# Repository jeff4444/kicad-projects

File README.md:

# KiCad Projects

A collection of custom PCB designs created in KiCad for various electronics projects.

## Projects

### � [Project Lux - Free-Space Optical Audio Link](./FSO/)
A laser-based audio communication system developed for the Howard University **IEEE H.O.P.E. (Hands-On PCB Engineering)** Project (Fall 2025). This sophisticated project demonstrates optical communication principles by transmitting high-fidelity audio over a laser beam.

#### [Transmitter Board](./FSO/Transmitter%20board/)
Modulates a 3.5mm audio input signal onto a laser diode using a transconductance stage with op-amps and transistors.

#### [Receiver Board](./FSO/Receiver%20board/)
Uses **BPW34** photodiodes with a transimpedance amplifier (TIA), voltage pre-amplification via **LM358**, and a **PAM8403D** Class-D audio amplifier to drive speakers.

---

### �🔊 [Audio Amplifier](./audio_amplifier/)
A low voltage audio power amplifier board based on the **LM386** IC. Perfect for small speaker applications requiring simple audio amplification from line-level sources.

### 📡 [Proximity Sensor](./proximity_sensor/)
An LED bar graph display board using the **LM3914** dot/bar display driver. Provides a visual representation of an analog signal level through a 10-LED bar graph display.

### 🤖 Recyclobot System
The Recyclobot is a robotics project consisting of two main PCBs:

#### [Controller](./recyclobot/controller/)
An RF remote control encoder board using the **HT12E** serial encoder IC. This board encodes button presses and transmits commands wirelessly to the motherboard.

#### [Motherboard](./recyclobot/motherboard/)
The main control board for the Recyclobot, featuring an **L293D** quadruple half-H motor driver. Receives wireless commands and controls DC motors for robot movement.

---

## Directory Structure

```
kicad-projects/
├── FSO/                 # Project Lux - Free-space optical audio link
│   ├── Receiver board/  # Photodiode array + TIA + audio amp
│   └── Transmitter board/ # Laser modulation circuit
├── audio_amplifier/     # LM386 audio amplifier board
├── proximity_sensor/    # LM3914 LED bar graph display
└── recyclobot/
    ├── controller/      # HT12E RF remote encoder
    └── motherboard/     # L293D motor driver board
```

## Getting Started

Each project directory contains:
- `.kicad_sch` - Schematic file
- `.kicad_pcb` - PCB layout file
- `.kicad_pro` - Project file
- `board.png` - Visual preview of the PCB design
- `gerbers/` - Manufacturing files (where available)

Open the `.kicad_pro` file in KiCad 8.0 or later to view and edit the designs.

## License

Personal electronics projects.

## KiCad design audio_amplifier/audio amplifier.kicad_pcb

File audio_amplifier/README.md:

# Audio Amplifier

A compact low voltage audio power amplifier PCB based on the **LM386** integrated circuit.

## Overview

This board provides simple audio amplification suitable for driving small speakers from line-level audio sources. The LM386 is a popular choice for battery-powered audio applications due to its low power consumption and minimal external component requirements.

## Key Features

- **LM386 Audio Power Amplifier IC**
  - Wide operating voltage range: 4V to 12V
  - Built-in gain control (20-200)
  - Low quiescent current for battery operation
  
- **Connectors for:**
  - Audio input
  - Speaker output
  - Power supply

## Specifications

| Parameter | Value |
|-----------|-------|
| Main IC | LM386 |
| Operating Voltage | 4V - 12V |
| Power Output | ~1W (into 8Ω @ 12V) |
| Package | DIP-8 |

## Applications

- Portable audio devices
- DIY speaker projects
- Guitar practice amplifiers
- Intercom systems
- Audio signal boosters

## Files

- `audio amplifier.kicad_sch` - Schematic
- `audio amplifier.kicad_pcb` - PCB layout
- `audio amplifier.kicad_pro` - KiCad project file
- `gerber_gen/` - Manufacturing files

## References

- [LM386 Datasheet (TI)](http://www.ti.com/lit/ds/symlink/lm386.pdf)

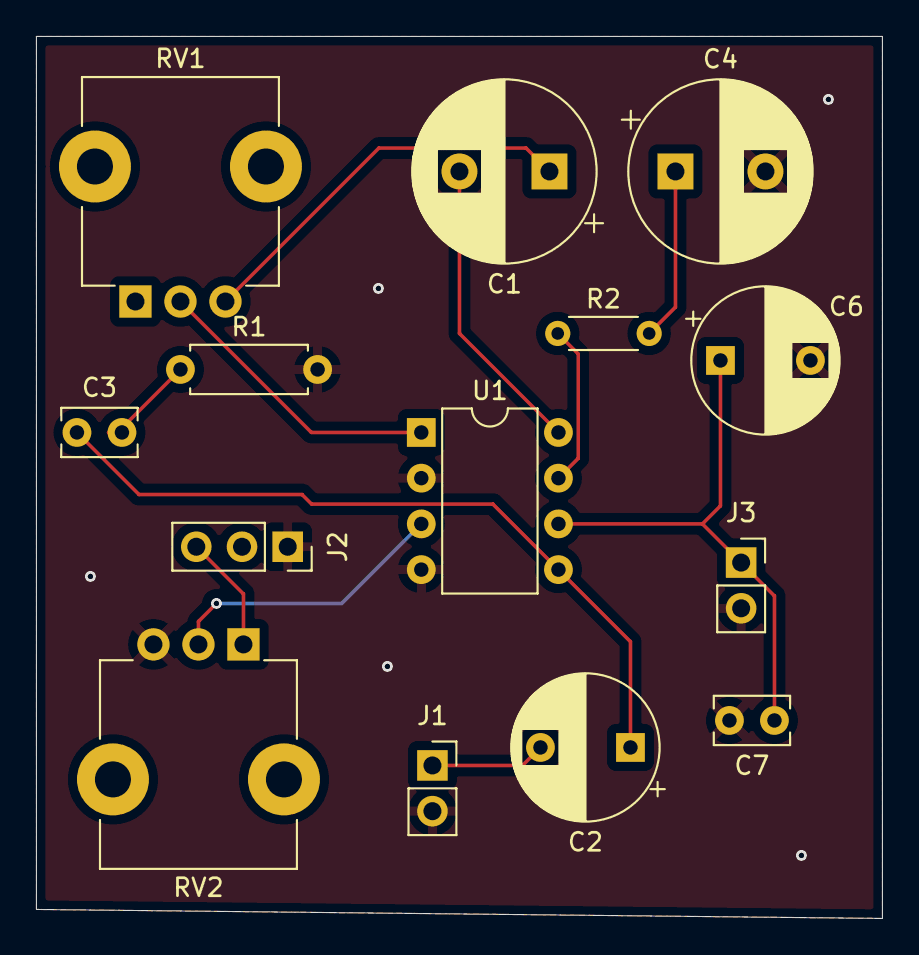
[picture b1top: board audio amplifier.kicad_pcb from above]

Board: 2 copper layers, 47.0 x 49.0 mm, 14 parts (0 on the bottom side), 12 nets.

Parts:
C1, C4: C_Polarized_US; CP_Radial_D10.0mm_P5.00mm
C2, C6: C_Polarized_US; CP_Radial_D8.0mm_P5.00mm
C3, C7: C; C_Rect_L4.0mm_W2.5mm_P2.50mm
J1, J3: Conn_01x02_Socket; PinSocket_1x02_P2.54mm_Vertical
J2: Conn_01x03_Socket; PinSocket_1x03_P2.54mm_Vertical
R1: R_US; R_Axial_DIN0207_L6.3mm_D2.5mm_P7.62mm_Horizontal
R2: R_US; R_Axial_DIN0204_L3.6mm_D1.6mm_P5.08mm_Horizontal
RV1, RV2: R_Potentiometer_US; Potentiometer_TT_P0915N
U1: LM386; DIP-8_W7.62mm

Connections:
+9V: C6.1, C7.1, J3.1, U1.6 (V+)
GND: C4.2, C6.2, C7.2, J1.2, J2.1, J3.2, R1.2, RV2.3, U1.2 (-), U1.4 (GND)
unnamed: C1.1, RV1.3
unnamed: C1.2, U1.8 (GAIN)
unnamed: C2.1, C3.1, U1.5
unnamed: C3.2, R1.1
unnamed: C4.1, R2.2
unnamed: C2.2, J1.1
unnamed: J2.3, RV2.1
unnamed: RV1.2, U1.1 (GAIN)
unnamed: RV2.2, U1.3 (+)
unnamed: R2.1, U1.7 (BYPASS)

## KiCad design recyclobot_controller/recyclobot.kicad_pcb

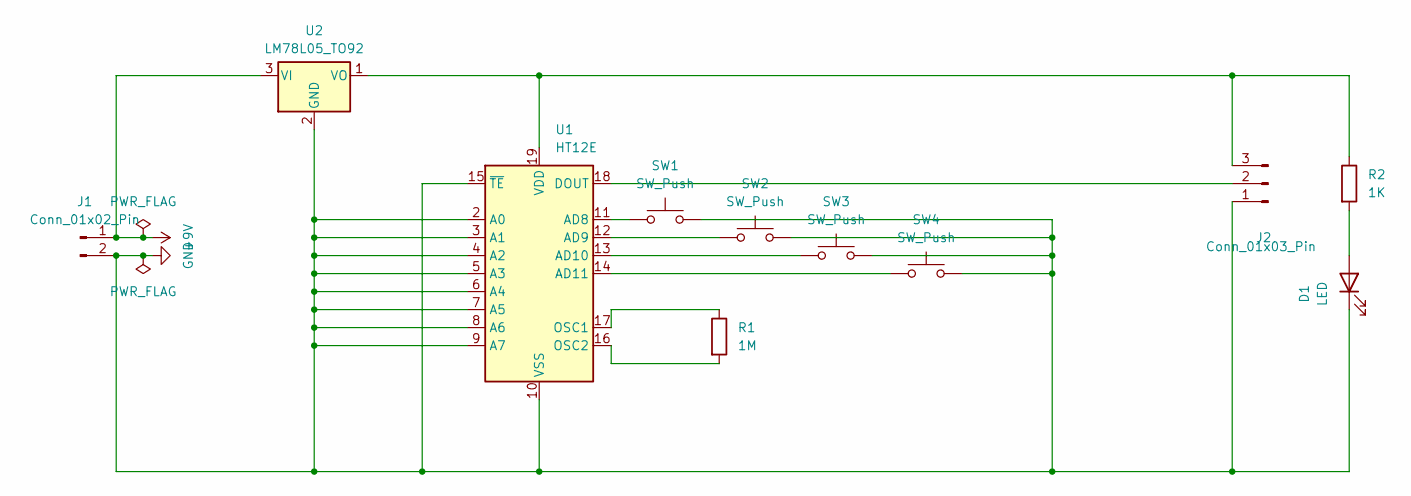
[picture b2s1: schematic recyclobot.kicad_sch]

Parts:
D1: LED; LED_D5.0mm
J1: Conn_01x02_Pin; PinSocket_1x02_P2.54mm_Vertical
J2: Conn_01x03_Pin; PinSocket_1x03_P2.54mm_Vertical
R1: 1M; R_Axial_DIN0207_L6.3mm_D2.5mm_P10.16mm_Horizontal
R2: 1K; R_Axial_DIN0207_L6.3mm_D2.5mm_P10.16mm_Horizontal
SW1, SW2, SW3, SW4: SW_Push; SW_Tactile_Straight_KSA0Axx1LFTR
U1: HT12E; SOP-20_7.5x12.8mm_P1.27mm
U2: LM78L05_TO92; TO-92_Inline_W4.0mm_Horizontal_FlatSideUp

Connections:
+9V: J1.1, U2.3 (VI)
GND: D1.1 (K), J1.2, J2.1, SW1.2, SW2.2, SW3.2, SW4.2, U1.2 (A0), U1.3 (A1), U1.4 (A2), U1.5 (A3), U1.6 (A4), U1.7 (A5), U1.8 (A6), U1.9 (A7), U1.10 (VSS), U1.15 (~TE), U2.2 (GND)
unnamed: D1.2 (A), R2.2
unnamed: J2.2, U1.18 (DOUT)
unnamed: J2.3, R2.1, U1.19 (VDD), U2.1 (VO)
unnamed: SW1.1, U1.11 (AD8)
unnamed: SW2.1, U1.12 (AD9)
unnamed: SW3.1, U1.13 (AD10)
unnamed: SW4.1, U1.14 (AD11)
unnamed: R1.1, U1.17 (OSC1)
unnamed: R1.2, U1.16 (OSC2)

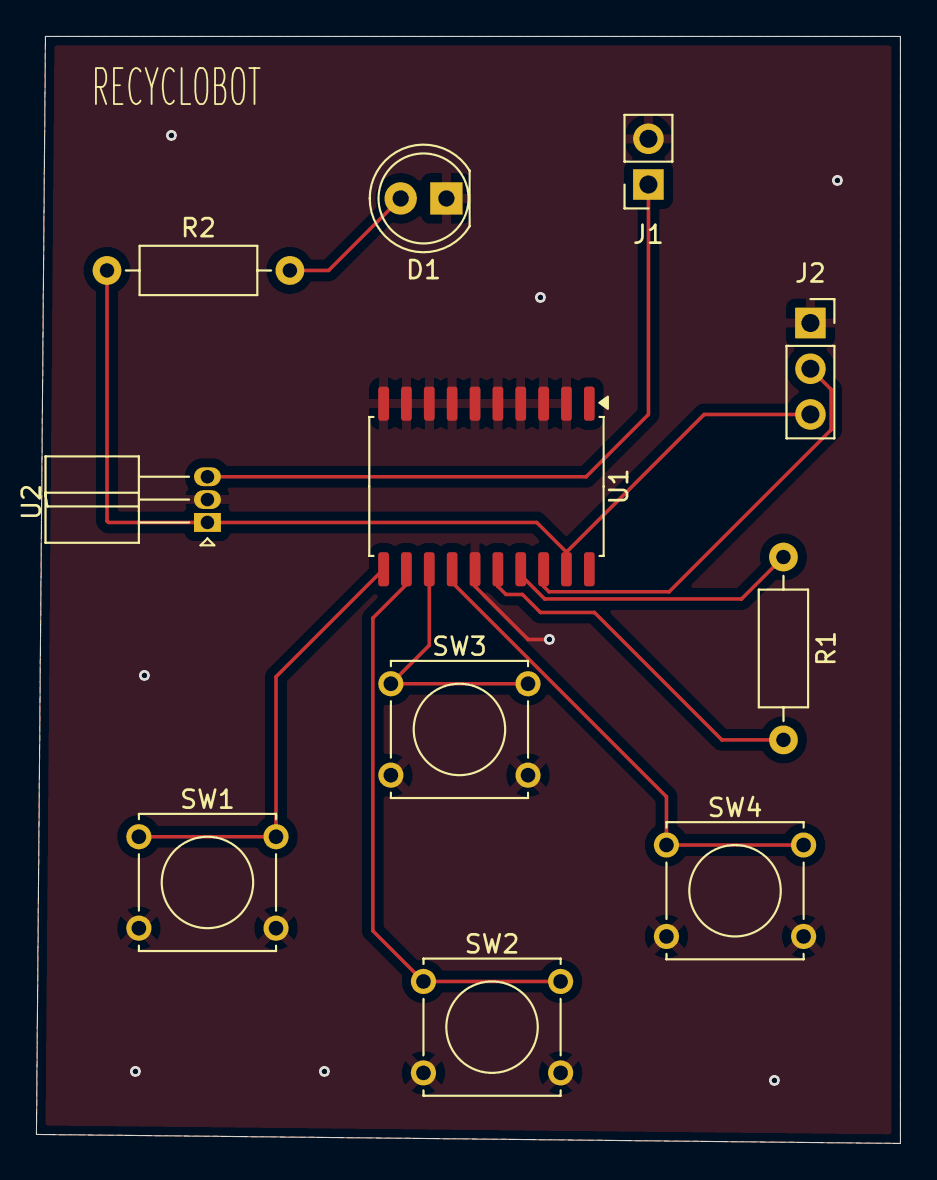
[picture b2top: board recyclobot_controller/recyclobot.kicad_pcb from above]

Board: 2 copper layers, 48.0 x 61.5 mm, 11 parts (0 on the bottom side), 11 nets.

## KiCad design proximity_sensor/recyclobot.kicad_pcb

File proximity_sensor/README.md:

# Proximity Sensor Display

An LED bar graph display PCB using the **LM3914** dot/bar display driver IC.

## Overview

This board provides a visual 10-LED bar graph display to represent an analog signal level. The LM3914 scales the input voltage linearly across its outputs, illuminating LEDs progressively as the signal increases. This is commonly used with proximity/distance sensors to provide a visual indication of signal strength or distance.

## Key Features

- **LM3914 Dot/Bar Display Driver IC**
  - 10 individually controlled LED outputs
  - Linear scale display
  - Selectable dot or bar display mode
  - Internal voltage reference
  
- **10 LEDs** for visual signal representation

- **Connectors for:**
  - Analog signal input
  - Power supply

## Specifications

| Parameter | Value |
|-----------|-------|
| Main IC | LM3914 |
| Display Mode | Dot or Bar (configurable) |
| LED Outputs | 10 |
| Package | DIP-18 |
| Operating Voltage | 3V - 25V |

## Applications

- Proximity/distance sensor displays
- Audio level meters (VU meters)
- Battery level indicators
- Signal strength meters
- Temperature displays

## How It Works

The LM3914 contains a precision 10-step voltage divider that compares the input signal against internal reference points. As the input voltage rises, more LEDs illuminate to provide a visual representation of the signal magnitude.

## Files

- `recyclobot.kicad_sch` - Schematic
- `recyclobot.kicad_pcb` - PCB layout
- `gerbers/` - Manufacturing files

## References

- [LM3914 Datasheet (TI)](https://www.ti.com/lit/ds/symlink/lm3914.pdf)

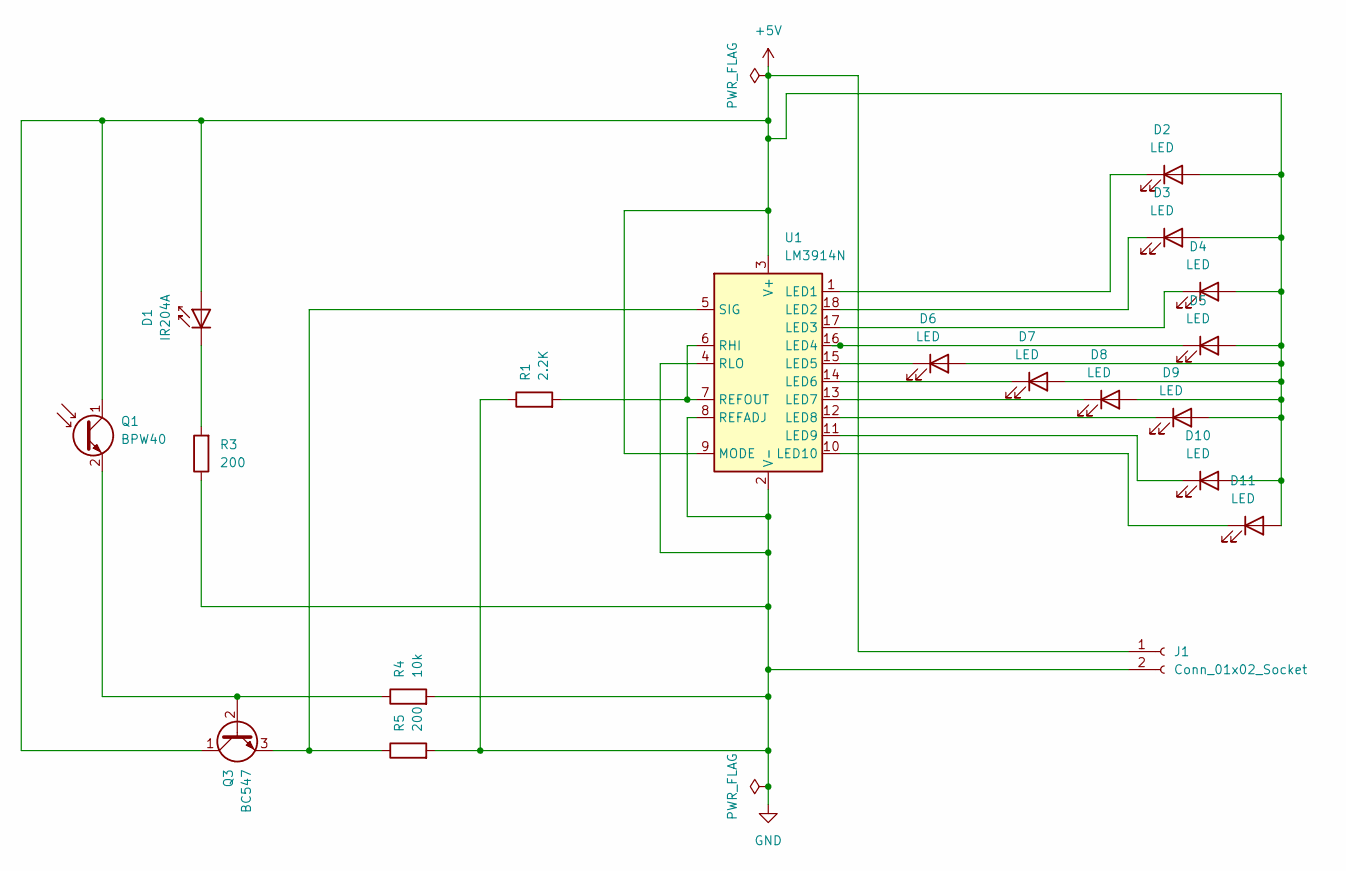
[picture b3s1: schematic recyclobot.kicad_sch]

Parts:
D1: IR204A; LED_D3.0mm_IRBlack
D2, D3, D4, D5, D6, D7, D8, D9, D10, D11: LED; LED_D3.0mm
J1: Conn_01x02_Socket; PinSocket_1x02_P2.54mm_Vertical
Q1: BPW40; LED_D5.0mm_Clear
Q3: BC547; TO-92_Inline
R1: 2.2K; R_Axial_DIN0204_L3.6mm_D1.6mm_P7.62mm_Horizontal
R3, R5: 200; R_Axial_DIN0204_L3.6mm_D1.6mm_P7.62mm_Horizontal
R4: 10k; R_Axial_DIN0204_L3.6mm_D1.6mm_P7.62mm_Horizontal
U1: LM3914N; DIP-18_W7.62mm

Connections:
+5V: D1.2 (A), D2.2 (A), D3.2 (A), D4.2 (A), D5.2 (A), D6.2 (A), D7.2 (A), D8.2 (A), D9.2 (A), D10.2 (A), D11.2 (A), J1.1, Q1.1 (C), Q3.1 (C), U1.3 (V+), U1.9 (MODE)
GND: J1.2, R1.1, R3.1, R4.2, R5.2, U1.2 (V-), U1.4 (RLO), U1.8 (REFADJ)
unnamed: D1.1 (K), R3.2
unnamed: D2.1 (K), U1.1 (LED1)
unnamed: D3.1 (K), U1.18 (LED2)
unnamed: D4.1 (K), U1.17 (LED3)
unnamed: D5.1 (K), U1.16 (LED4)
unnamed: D6.1 (K), U1.15 (LED5)
unnamed: D7.1 (K), U1.14 (LED6)
unnamed: D8.1 (K), U1.13 (LED7)
unnamed: D9.1 (K), U1.12 (LED8)
unnamed: D10.1 (K), U1.11 (LED9)
unnamed: D11.1 (K), U1.10 (LED10)
unnamed: Q1.2 (E), Q3.2 (B), R4.1
unnamed: Q3.3 (E), R5.1, U1.5 (SIG)
unnamed: R1.2, U1.6 (RHI), U1.7 (REFOUT)

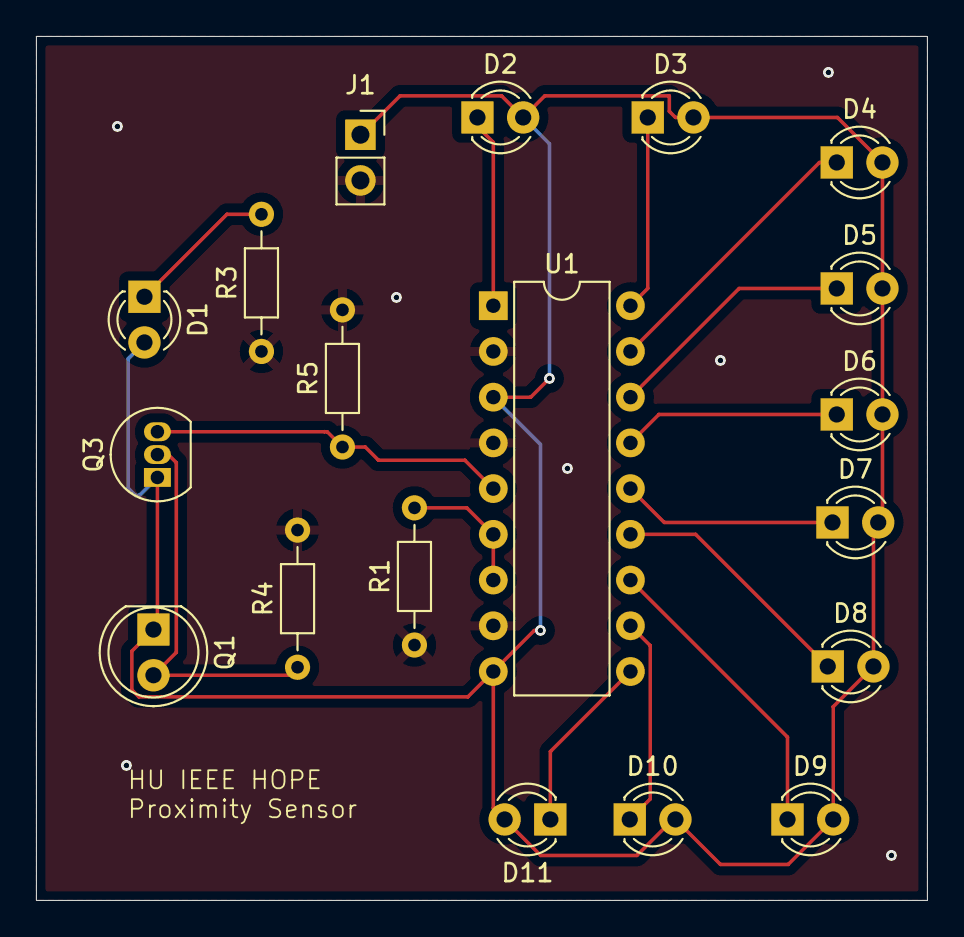
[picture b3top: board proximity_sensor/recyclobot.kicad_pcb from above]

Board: 2 copper layers, 49.5 x 48.0 mm, 19 parts (0 on the bottom side), 16 nets.

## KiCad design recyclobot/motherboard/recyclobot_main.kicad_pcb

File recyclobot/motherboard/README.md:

# Recyclobot Motherboard

The main motor driver PCB for the Recyclobot, featuring the **L293D** quadruple half-H motor driver IC.

## Overview

This board is the central control unit for the Recyclobot project. It receives wireless commands from the remote controller and drives DC motors to move the robot. The L293D provides bidirectional control for two DC motors with built-in protection diodes.

## Key Features

- **L293D Quadruple Half-H Motor Driver IC**
  - Dual full-bridge configuration for 2 motors
  - Bidirectional motor control (forward/reverse)
  - Built-in flyback diodes
  - Separate logic and motor supply voltages
  
- **LED indicators** for power and status

- **Connectors for:**
  - DC motor outputs (2 motors)
  - RF receiver module
  - Power supply
  - Sensor inputs

## Specifications

| Parameter | Value |
|-----------|-------|
| Main IC | L293D |
| Motor Channels | 2 (bi-directional) |
| Logic Voltage | 5V |
| Motor Voltage | 4.5V - 36V |
| Output Current | 600mA per channel (1.2A peak) |
| Package | DIP-16 |

## System Integration

This motherboard receives commands from the **Recyclobot Controller** via wireless RF link.

```
┌─────────────────┐                   ┌─────────────────┐
│   Controller    │     RF Signal     │   Motherboard   │
│     (HT12E)     │ ─────────────────▶│     (L293D)     │
└─────────────────┘                   └────────┬────────┘
                                               │
                                    ┌──────────┴──────────┐
                                    │                     │
                              ┌─────▼─────┐         ┌─────▼─────┐
                              │  Motor 1  │         │  Motor 2  │
                              │  (Left)   │         │  (Right)  │
                              └───────────┘         └───────────┘
```

## Motor Control Truth Table

| EN | IN1 | IN2 | Motor Action |
|----|-----|-----|--------------|
| H  | L   | H   | Forward      |
| H  | H   | L   | Reverse      |
| H  | L   | L   | Coast/Stop   |
| H  | H   | H   | Brake        |
| L  | X   | X   | Disabled     |

## Files

- `recyclobot_main.kicad_sch` - Schematic
- `recyclobot_main.kicad_pcb` - PCB layout
- `gerbers/` - Manufacturing files

## References

- [L293D Datasheet (TI)](http://www.ti.com/lit/ds/symlink/l293.pdf)

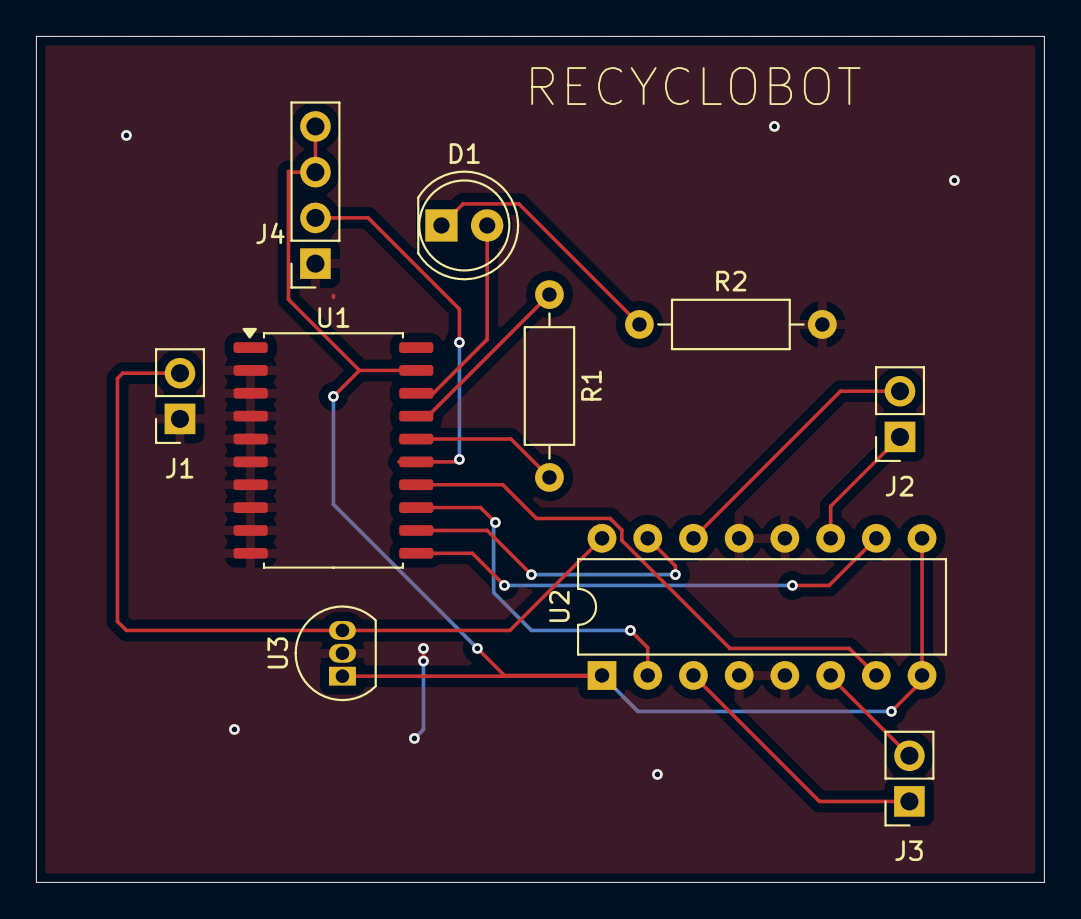
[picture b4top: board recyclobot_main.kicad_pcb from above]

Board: 2 copper layers, 56.0 x 47.0 mm, 10 parts (0 on the bottom side), 16 nets.

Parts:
D1: LED; LED_D5.0mm
J1, J2, J3: Conn_01x02_Socket; PinSocket_1x02_P2.54mm_Vertical
J4: Conn_01x04_Socket; PinSocket_1x04_P2.54mm_Vertical
R1: 33K; R_Axial_DIN0207_L6.3mm_D2.5mm_P10.16mm_Horizontal
R2: 1K; R_Axial_DIN0207_L6.3mm_D2.5mm_P10.16mm_Horizontal
U1: HT12D; SOP-20_7.5x12.8mm_P1.27mm
U2: L293D; DIP-16_W7.62mm
U3: LM78L05_TO92; TO-92_Inline

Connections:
+9V: J1.2, U2.16 (VCC1), U3.3 (VI)
GND: J1.1, J4.1, R2.2, U1.2 (A0), U1.3 (A1), U1.4 (A2), U1.5 (A3), U1.6 (A4), U1.7 (A5), U1.8 (A6), U1.9 (A7), U1.10 (VSS), U2.4 (GND), U2.5 (GND), U2.12 (GND), U2.13 (GND), U3.2 (GND)
unnamed: D1.2 (A), U1.18 (VT)
unnamed: D1.1 (K), R2.1
unnamed: J2.1, U2.11 (3Y)
unnamed: J2.2, U2.14 (4Y)
unnamed: J3.1, U2.3 (1Y)
unnamed: J3.2, U2.6 (2Y)
unnamed: J4.2, U1.15 (DIN)
unnamed: J4.3, J4.4, U1.19 (VDD), U2.1 (EN1,2), U2.8 (VCC2), U2.9 (EN3,4), U3.1 (VO)
unnamed: U1.11 (D8), U2.10 (3A)
unnamed: U1.12 (D9), U2.15 (4A)
unnamed: U1.13 (D10), U2.2 (1A)
unnamed: U1.14 (D11), U2.7 (2A)
unnamed: R1.1, U1.17 (OSC1)
unnamed: R1.2, U1.16 (OSC2)

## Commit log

2025-12-30 Add prev projects
2025-12-30 Add readmes
